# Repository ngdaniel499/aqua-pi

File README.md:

# AquaPi
Documentation for the Raspberry Pi based water quality monitoring system created by Daniel P. Harrison

## Pi first time setup
### Flash OS
#### Windows
Download Raspberry pi imager https://www.raspberrypi.com/software/

Raspberry Pi Device: Raspberry Pi 1

Operating System: Raspberry PI OS Lite (32-BIT)
	
 	PRETTY_NAME="Raspbian GNU/Linux 12 (bookworm)"
	NAME="Raspbian GNU/Linux"
	VERSION_ID="12"
	VERSION="12 (bookworm)"
	VERSION_CODENAME=bookworm
	ID=raspbian
	ID_LIKE=debian
	HOME_URL="http://www.raspbian.org/"
	SUPPORT_URL="http://www.raspbian.org/RaspbianForums"
	BUG_REPORT_URL="http://www.raspbian.org/RaspbianBugs"
	 
OS Customisation settings: 

	Services>Enable SSH, 

	General>Set username/pw, 

	General>Configure Wireless LAN: add SSID/pin, 

	General>Set Locale settings>Time Zone: Sydney, 

	General>Set Locale settings>Keyboard Layout: US

### RPi setup
	sudo ip link set eth1 down
 
  	sudo ip link set usb0 down
  
	sudo apt-get update

	sudo apt-get upgrade

#### configure startup for 1-wire and wlan0
	sudo nano /etc/rc.local

	#add the following lines above exit 0

	#disable ethernet (remove these ip link lines if you want to use ethernet)
	ip link set eth1 down

 	ip link set eth0 down
     
	sudo modprobe w1-gpio
	
	sudo modprobe w1-therm

#### Turn on 1-wire

Refernce: https://learn.adafruit.com/adafruits-raspberry-pi-lesson-11-ds18b20-temperature-sensing/ds18b20

	sudo raspi-config

		Interfacing Options > 1-Wire > Yes

	sudo reboot

#### Install aqua-pi files and dependencies and setup virtual environment
	sudo apt install git
 
  	cd ~
  
 	git clone https://github.com/ngdaniel499/aqua-pi.git
 
	cd ~/aqua-pi

	sudo apt-get install python3 python3-pip

	python3 -m venv .venv

	source .venv/bin/activate

	pip install -r requirements.txt
#### Setup Crontab with debugging log
	# Run AquaPi measurement (main) job every 15 minutes
	*/15 * * * * /home/pi/aqua-pi/python-scripts/cron-main.sh
	
	# Run Pump script every 15 minutes with a 7 minute offset
	7-59/15 * * * * /home/pi/aqua-pi/python-scripts/cron-pump.sh

 ## Webserver
 daniel@debian:cat /etc/systemd/system/aquapi-frontend.service
	 
	[Unit]
	Description=AquaPi Frontend (Next.js)
	
	After=network.target
	
	[Service]
	User=daniel
	Group=daniel
	WorkingDirectory=/home/daniel/aqua-pi/webserver/frontend
	ExecStart=/usr/bin/npm run start -- -p 3001
	Restart=always
	RestartSec=5
	Environment=NODE_ENV=production
	
	[Install]
	WantedBy=multi-user.target

daniel@debian:~/aqua-pi/webserver$ cat /etc/systemd/system/aquapi-backend.service
	[Unit]
	Description=AquaPi Backend (Gunicorn)
	After=network.target
	
	[Service]
	User=daniel
	Group=daniel
	WorkingDirectory=/home/daniel/aqua-pi/webserver/backend
	Environment="PATH=/home/daniel/aqua-pi/webserver/backend/venv/bin"
	ExecStart=/home/daniel/aqua-pi/webserver/backend/venv/bin/gunicorn --bind 127.0.0.1:8000 app:app
	Restart=always
	RestartSec=5
	
	[Install]
	WantedBy=multi-user.target

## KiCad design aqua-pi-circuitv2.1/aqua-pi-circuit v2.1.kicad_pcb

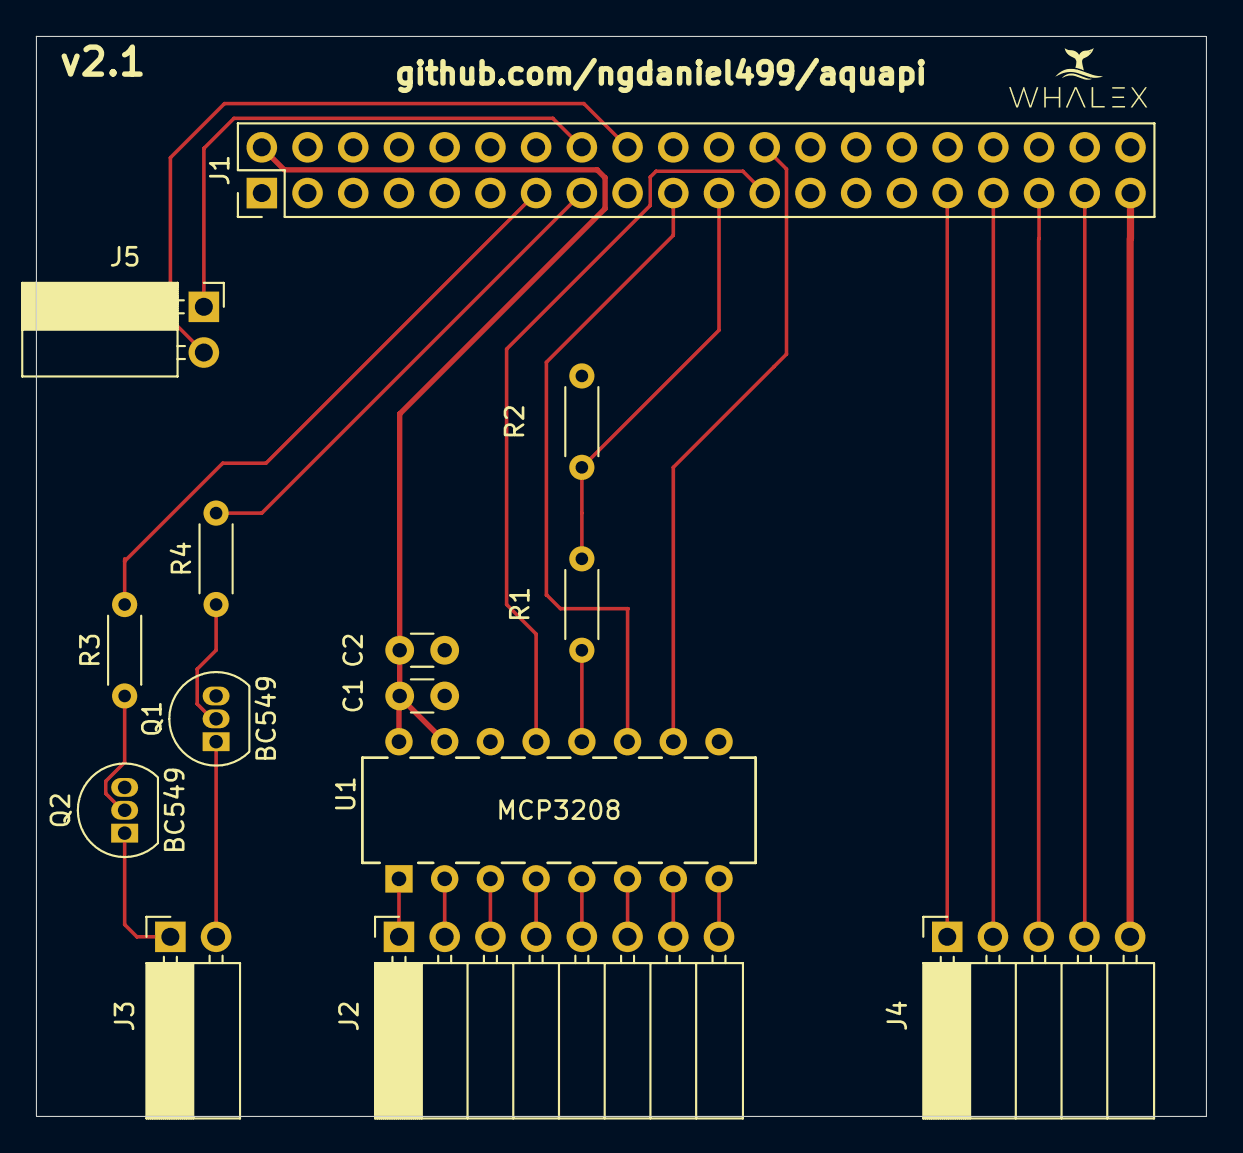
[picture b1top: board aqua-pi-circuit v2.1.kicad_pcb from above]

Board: 2 copper layers, 65.0 x 60.0 mm, 14 parts (0 on the bottom side), 27 nets.

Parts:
C1: 100nF; C_Disc_D3.0mm_W1.6mm_P2.50mm
C2: 1uF; C_Disc_D3.0mm_W1.6mm_P2.50mm
J1: Conn_02x20_Odd_Even; PinHeader_2x20_P2.54mm_Vertical
J2: Conn_01x08_Pin; PinSocket_1x08_P2.54mm_Horizontal
J3: Conn_01x02_Pin; PinSocket_1x02_P2.54mm_Horizontal
J4: Conn_01x05_Pin; PinSocket_1x05_P2.54mm_Horizontal
J5: Conn_01x02; PinSocket_1x02_P2.54mm_Horizontal
Q1, Q2: BC549; TO-92_Inline
R1, R3, R4: 1k; R_Axial_DIN0204_L3.6mm_D1.6mm_P5.08mm_Horizontal
R2: 2k; R_Axial_DIN0204_L3.6mm_D1.6mm_P5.08mm_Horizontal
U1: MCP3208; PDIP16_300MC_MCH

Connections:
GND: C1.1, C2.1, J1.9, J1.25, J1.39, J4.5, Q1.3 (E), Q2.3 (E), R2.1, U1.9 (DGND), U1.14 (AGND)
unnamed: C1.2, C2.2, J1.2, U1.15 (Vref), U1.16 (Vdd)
unnamed: J1.13, R3.2
unnamed: J1.15, R4.2
unnamed: J1.16, J5.1
unnamed: J1.18, J5.2
unnamed: J1.19, U1.11 (Din)
unnamed: J1.21, R1.1, R2.2
unnamed: J1.23, U1.13 (CLK)
unnamed: J1.24, U1.10 (~CS/SHDN)
unnamed: J1.31, J4.1
unnamed: J1.33, J4.2
unnamed: J1.35, J4.3
unnamed: J1.37, J4.4
unnamed: J2.1, U1.1 (CH0)
unnamed: J2.2, U1.2 (CH1)
unnamed: J2.3, U1.3 (CH2)
unnamed: J2.4, U1.4 (CH3)
unnamed: J2.5, U1.5 (CH4)
unnamed: J2.6, U1.6 (CH5)
unnamed: J2.7, U1.7 (CH6)
unnamed: J2.8, U1.8 (CH7)
unnamed: J3.1, Q2.1 (C)
unnamed: J3.2, Q1.1 (C)
unnamed: Q1.2 (B), R4.1
unnamed: Q2.2 (B), R3.1
unnamed: R1.2, U1.12 (Dout)

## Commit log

2024-08-19 added components list draft
2024-08-19 update components list
2024-08-19 renamed files
2024-09-05 Added original code given by Daniel harrison
2024-09-05 Old OS deprecated. cant install build dependencies / kernel headers. Updated to run on Raspberry Pi OS lite (Raspbian GNU / Linux 12 (bookworm)) Updated code to work with python3 Added pip requiremen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
2024-09-05 Updated readme with first time setup directions for new OS
2024-09-05 fixed README formatting
2024-09-05 renamed from final.py to main.py properly, added data folder
2024-09-05 updated formatting
2024-09-05 renamed FINAL_CODE to python-scripts
2024-09-05 Added Probe specsheets / manuals
2024-09-06 Update README.md
    crotnab
2024-09-06 Update README.md
    OS description
2024-09-11 renamed
2024-09-12 renamed Probe to probe
2024-09-12 Probes>probes
2024-09-12 added data folder to upconfig to prepare for web upload, added results plotter for chla
2024-09-12 updated Upconfig with data
2024-09-12 fixed data> data_dir
2024-09-12 Fixed data in upconfig and main.py
2024-09-12 added .gitignore for pycache
2024-09-12 pycache removed
2024-09-12 added data folder to gitignore
2024-09-12 added upload log and list to .gitignore
2024-09-12 added https upload to AWS web server
2024-09-12 updated requirements.txt
2024-09-12 draw results notebook for troubleshooting data, drawresults.py to save graph for all files in a given directory
2024-09-12 removed uploaddata from gitignore
2024-09-13 reconfiguration
2024-09-13 deprecated ftp server
2024-09-13 changed upload data to account for newest file updating
2024-09-13 renamed data dir
2024-09-13 added exception case for dead server
2024-09-17 moved cronjob to /python-scripts/script.sh, updated requirements.txt for only aquapi requirements (drawresults, etc wont work without new installations but not needed for rpi), updated README.md
2024-09-17 script.sh>cronjob.sh more descriptive
2024-09-25 renamed scripts in prep for pump script
2024-09-25 removed deprecated code
2024-09-25 untested pump code
2024-09-25 working pump and cron script for pump
2024-09-25 removed deprecated pump setup / ftup from main.py
2024-09-25 Update README.md. fixed .venv and added new crontab line to run pump at 15mins offset by 7m
2024-09-25 fixed readme crontab
2024-10-09 Create file
2024-10-09 Delete python-scripts/data/file
    removed placeholder file (to create directory)
2024-10-09 Create .gitignore for empty data directory
2024-10-17 added webserver files
2024-10-17 rename CS109 probe docx to remove funky chars
2024-10-19 changed readme to edit /etc/network/interfaces instead of rc.local to prioritise wlan0 instead of disablineg eth
2024-10-19 reverted back to disable eth0 eth1 usb0
2024-10-19 remove usb0 down error
2024-11-04 removed turb
2024-11-05 test script
2024-11-05 added Upconfig.cfg to gitignore
2024-11-06 added calibration sheet (calibrated against 400ppb RWT at 10x gain)
2024-11-26 added revamped aquapi circuit files
2024-11-27 added a moving average to the chlorophyll ADC, added gain switching functionality
2024-11-27 added upconfig to .gitignore and moved Upconfig.cfg template to home directory
2024-11-27 fixed formatting
2024-11-27 debug
2024-11-27 debug MA function
2024-11-27 added individual and cumulative response for debugging
2024-11-27 tuning average settings
2024-11-27 testing different windows
2024-11-27 central limit theorem implentation for noise attenuation
2024-11-27 debug clt
2024-11-28 added gain switching to main, changed SNSR to snsr.py, added running mean calculation, running variance/error calculation
2024-11-28 added verbose prints
2024-12-10 sync pin config across devices
2024-12-13 fixed typo cal>volts
2024-12-20 added calibration data, added multi-calibration between different gain values, renamed Upconfig to Upconfig_template.cfg
2024-12-27 setup first time setup directories
2024-12-27 added first time setup files
2024-12-27 added some comments for directories
2024-12-27 moved app.log into logs
2024-12-27 stopped rtacking log files
2024-12-28 updated to work on local server
2024-12-28 newest files now show at the top of the webpage
2024-12-28 added archived function to separate current and old files
2024-12-29 Create aquapi2
    order plan
2024-12-29 added front end react with upgraded dashboard for easy viewing
2024-12-29 updated visuals and removed unused variables
2025-03-06 temperature, snsr.py cleanup
2025-03-07 udpated for formatting
2025-03-07 fixed averaging
2025-03-07 changed to display CI for actual cal temp
2025-03-07 removed unused variablels from outpubt
2025-03-07 exp branch with new temp
2025-03-07 updated exp temp thing
2025-03-07 new Upconfig for AP1
2025-03-07 removed upconfig from tracking
2025-03-07 fixed snsr.py for new temp
2025-03-07 udpate
2025-03-07 working with ap01
2025-03-07 new upconfig template with ap01 values
2025-03-07 commented out cond/tempsal probe code and removed turbiditiy code cleanup
2025-03-07 commented out debugging print
2025-03-07 added print for temperature range 95%CI
2025-03-07 not sure if this is working
2025-03-08 small fix to comment
2025-05-29 updated run pump with timed, on and off functions instead of true/false
2025-05-29 ujpdated upconfig pump run to off by default and addd an example test name to stationid
2025-05-30 moved cron-reconnect.sh inside directory
2025-05-30 added cronjob
2025-05-30 some ui components
2025-05-30 revamped reconnect script and collated log files
2025-06-01 added temperature calibration
2025-06-01 added temperature cal data and 2 point calibration set for quick estimate on experiment date
2025-07-01 updated cal sheet with data from CultureCronulla experiment
2025-07-01 removed legacy functions
2025-07-02 updated readchl and main to be consistent with the rest of the functions. and to calculate intercept cal properly.
2025-08-08 working culturecronnulla 2 version
2026-06-19 Update Flask secret key to use a placeholder
2026-06-19 Add systemd service configuration for AquaPi
2026-06-19 Format systemd service entries in README.md
